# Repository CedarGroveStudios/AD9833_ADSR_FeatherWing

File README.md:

# MOVED TO: CedarGroveStudios/PCB_AD9833_ADSR_FeatherWing
https://github.com/CedarGroveStudios/PCB_AD9833_ADSR_FeatherWing.git

# This repo will be retired 2022-12-01

# AD9833_ADSR_FeatherWing
### _An amplitude-controlled version of the original AD9833 Waveform Generator FeatherWing_

## Overview
The AD9833 ADSR FeatherWing project is a software and hardware extension of previous work done on the AD9833 Waveform Generator FeatherWing. The ADSR project adds output amplitude control to simulate the Attack-Decay-Sustain-Release envelope needed to simulate musical instrument sounds.
The AD9833 ADSR FeatherWing is an Adafruit Feather-compatible module. The Waveform Generator portion, controlled by SPI, produces an op-amp buffered sine, triangle, or square wave output with a practical frequency range of 0.5Hz to 100KHz with 0.1Hz resolution. The on-board AD5245 Digital Potentiometer is a 256-step 10K potentiometer controlled by I2C. This PCB version includes enhanced power supply noise reduction and an improved output buffer amplifier with higher gain-bandwidth product.

Example MIDI synthesizer and sweep generator code is provided in the repository (sweep example video: https://youtu.be/O1vMfLoCWzg). 
MIDI synthesizer and sweep generator code was tested with a Feather M4 Express using CircuitPython version 4.1.0 rc-1.

MIDI note input was received by a Classic MIDI Interface FeatherWing from a variety of MIDI sources. See https://github.com/CedarGroveStudios/Classic_MIDI_FeatherWing for details.

OSH Park shared PCB project: https://oshpark.com/shared_projects/nDZsxzWR

## AD5245 Digital Potentiometer for Envelope Control
Unlike using the Feather's internal DAC as a multiplying DAC by applying a waveform to the DAC's reference voltage input, the digital potentiometer doesn't require a reference bias, eliminating the distortion that happens when the DAC's reference voltage is less than about 1v. The digital potentiometer's internal MOSFET switches are biased differently than a DAC, allowing the AD5245 potentiometer to control voltage values between ground and Vcc.

The resulting envelope met the original design expectations for distortionless scaling of the waveform's amplitude. The only issue faced was limited I2C data transfer rates during short-duration envelope segments such as shown during the Sustain segment below.

The latest version of the envelope segment control algorithm was modified to use a fixed time interval approach rather than a variable time interval based on segment duration. In the newest code, the digital potentiometer updates regularly every 1ms during segment generation, a speed easily accommodated by CircuitPython and the Feather M4 Express.

## Primary Project Objectives
1)	Generate a smooth ADSR modulated waveform from the AD9833 across the audio spectrum (1Hz to 20KHz).  
2)	Implement with CircuitPython code.
3)  Develop CircuitPython libraries for the AD9833 and AD5245.
4)  Improve output bandwidth.
5)  Reduce power supply noise bleedthrough.
## Deliverables
1)	CircuitPython test, example, and library code
2)  Updated custom FeatherWing PCB  
  a) FeatherWing Implementation Chart  
  b) KiCAD schematic and board layout with Gerber code  
3)	OSH Park public shared project page
4)	GitHub public repository page
5)	Project description and report
## Concepts Learned
1)  The digital potentiometer approach is very viable and eliminates the multiplying DAC reference input bias distortion issue. 
2)  The digital potentiometer's 256-step resolution appears to be sufficient for artifactless envelope generation.
## Next Steps
  * Create a version of the PCB for the low-power AD9837 device (thanks to @jeffwurz).
  * Design a Eurorack-compatible version that provides MIDI and CV/Gate inputs.
  * Design a desktop test equipment version with display and selector knob.
  *	Incorporate the knowledge and experience gained in this project into the design of an Arbitrary Waveform Generator FeatherWing.

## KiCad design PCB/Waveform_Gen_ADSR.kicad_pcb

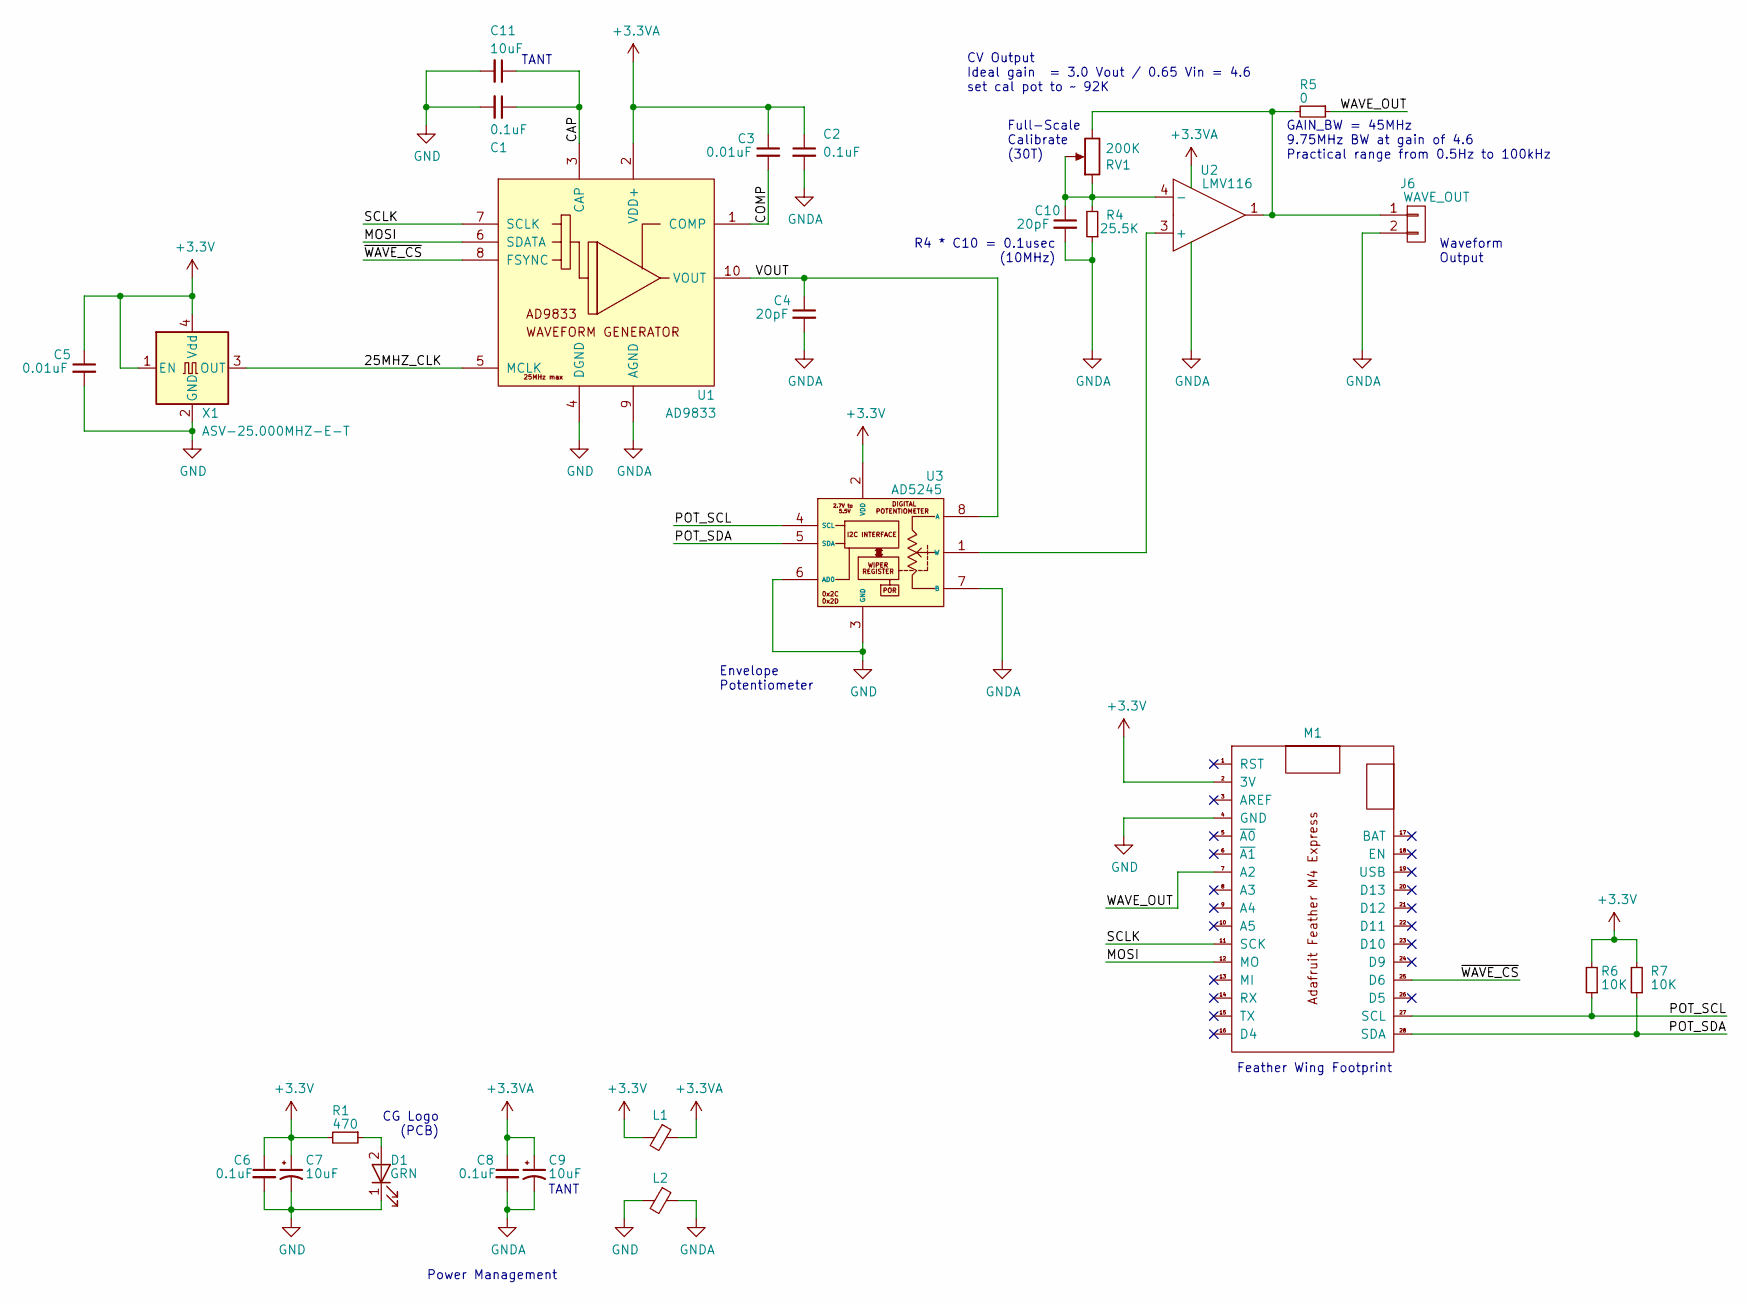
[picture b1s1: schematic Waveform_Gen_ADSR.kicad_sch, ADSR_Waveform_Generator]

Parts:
C1, C2, C6, C8: 0.1uF; C_0805
C3, C5: 0.01uF; C_0805
C4, C10: 20pF; C_0805
C7, C9, C11: 10uF; C_0805
D1: GRN; Cedar_Grove_logo_lighted
J6: WAVE_OUT; Pin_Header_Straight_1x02_Pitch2.54mm
L1, L2: 0; L_0805
M1: Feather_M4_Express; Adafruit_Feather_M4_Express_bare
R1: 470; R_0805
R4: 25.5K; R_0805
R5: 0; R_0805
R6, R7: 10K; R_0805
RV1: 200K; Potentiometer_Trimmer_Bourns_PV36W
U1: AD9833; MSOP-10_3x3mm_Pitch0.5mm
U2: LMV116; SOT-23-5_HandSoldering
U3: AD5245; SOT-23-8
X1: ASV-25.000MHZ-E-T; Oscillator_SMD_Abracon_ASV-4pin_7.0x5.1mm

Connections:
+3.3VA: C2.1, C3.1, C8.1, C9.1, L1.1, U1.2 (VDD+), U2.5 (VDD+)
+3V3: C5.1, C6.1, C7.1, L1.2, M1.2 (3V), R1.2, R6.2, R7.2, U3.2 (VDD), X1.1 (EN), X1.4 (Vdd)
/25MHZ_CLK: U1.5 (MCLK), X1.3 (OUT)
/CAP: C1.1, C11.1, U1.3 (CAP)
/COMP: C3.2, U1.1 (COMP)
/MOSI: M1.12 (MO), U1.6 (SDATA)
/POT_SCL: M1.27 (SCL), R6.1, U3.4 (SCL)
/POT_SDA: M1.28 (SDA), R7.1, U3.5 (SDA)
/SCLK: M1.11 (SCK), U1.7 (SCLK)
/VOUT: C4.1, U1.10 (VOUT), U3.8 (A)
/WAVE_OUT: M1.7 (A2), R5.1
/~WAVE_CS: M1.25 (D6), U1.8 (FSYNC)
GND: C1.2, C5.2, C6.2, C7.2, C11.2, D1.1 (K), L2.2, M1.4 (GND), U1.4 (DGND), U3.3 (GND), U3.6 (AD0), X1.2 (GND)
GNDA: C2.2, C4.2, C8.2, C9.2, C10.2, J6.2, L2.1, R4.1, U1.9 (AGND), U2.2 (VDD-), U3.7 (B)
unnamed: C10.1, R4.2, RV1.1, RV1.2, U2.4 (-)
unnamed: D1.2 (A), R1.1
unnamed: J6.1, R5.2, RV1.3, U2.1
unnamed: U2.3 (+), U3.1 (W)

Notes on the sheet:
GAIN_BW = 45MHz 9.75MHz BW at gain of 4.6 Practical range from 0.5Hz to 100kHz
TANT
CG Logo (PCB)
CV Output Ideal gain = 3.0 Vout / 0.65 Vin = 4.6 set cal pot to ~ 92K
R4 * C10 = 0.1usec (10MHz)
Full-Scale Calibrate (30T)
Power Management
Envelope Potentiometer
Waveform Output
Feather Wing Footprint

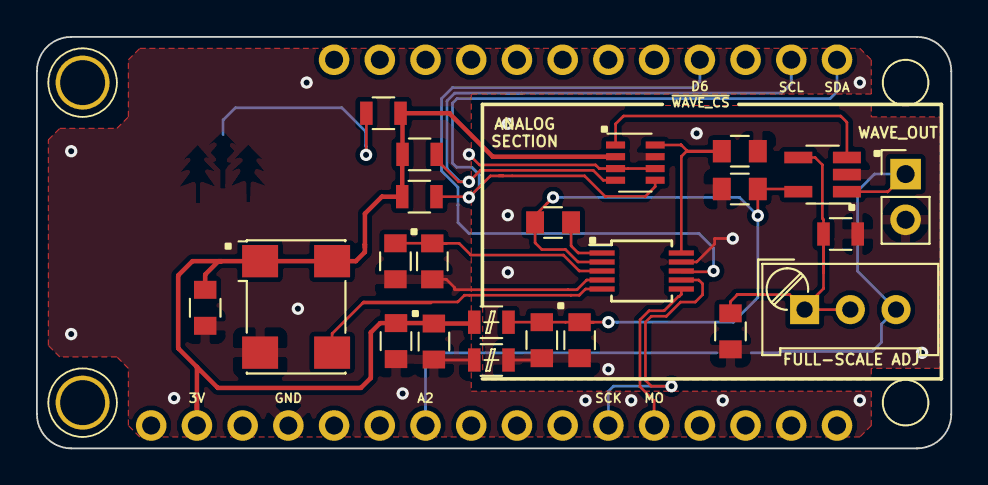
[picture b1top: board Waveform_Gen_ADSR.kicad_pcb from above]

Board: 2 copper layers, 50.8 x 22.9 mm, 26 parts (1 on the bottom side), 18 nets.

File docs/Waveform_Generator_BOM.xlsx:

Reference | Value | Desc | Footprint | DigiKey
C1 | 0.1uF | capacitor | 0805
C10 | 20pF | capacitor | 0805
C11 | 10uF | capacitor tantalum | 0805
C2 | 0.1uF | capacitor | 0805
C3 | 0.01uF | capacitor | 0805
C4 | 20pF | capacitor | 0805
C5 | 0.01uF | capacitor | 0805
C6 | 0.1uF | capacitor | 0805
C7 | 10uF | capacitor | 0805
C8 | 0.1uF | capacitor | 0805
C9 | 10uF | capacitor tantalum | 0805
D1 | GRN | LED | 1206
J6 | WAVE_OUT | 2-pin header | 1x02_Pitch2.54mm
R1 | 470 ohm | resistor | 0805
R4 | 25.5K | resistor | 0805
R6 | 10K | resistor | 0805
R7 | 10K | resistor | 0805
RV1 | 200K | potentiometer | Trimmer_Bourns_PV36W | https://www.digikey.com/products/en?keywords=490-2882-ND%20
U1 | AD9833 | waveform generator | MSOP-10_3x3mm_Pitch0.5mm | https://www.digikey.com/products/en?keywords=AD9833BRMZ-REEL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
U3 | AD5245 | digital potentiometer
U2 | LMV116 | op-amp | SOT-23-5
X1 | ASV-25.000MHZ-E-T | oscillator | ASV-4pin_7.0x5.1mm | https://www.digikey.com/products/en?keywords=535-10078-1-ND

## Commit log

2019-09-09 update version number
2019-09-09 working on layout
2019-09-10 update layout
2019-09-10 update PCB layout
2019-09-11 update layout; stack AD983x footprints
2019-09-11 update pcb layout; add stacked footprints; add sine logo
2019-09-12 update PCB layout; include support for AD9837
2019-09-14 change scope to support only AD9833
2019-10-14 update logo
2019-11-20 code update
2019-11-20 update photos
2019-11-20 update photos and board design files
2019-11-20 update FeatherWing Implementation Chart
2019-11-21 additional graphics
2019-12-26 update graphic
2021-07-12 update documents
2022-06-30 Update docs
2022-07-01 update kicad tables
2022-07-31 create backup
2022-09-02 update license
2022-10-12 move code to CircuitPython_AD5245
2022-10-13 add archive version
2022-11-15 Repository is moving to PCB_AD9833_ADSR_FeatherWing
2023-01-13 update kicad backup
2023-01-18 update footprints; 3d images
2023-01-25 update backup folder
2023-01-31 update backups
2023-02-08 update backup
